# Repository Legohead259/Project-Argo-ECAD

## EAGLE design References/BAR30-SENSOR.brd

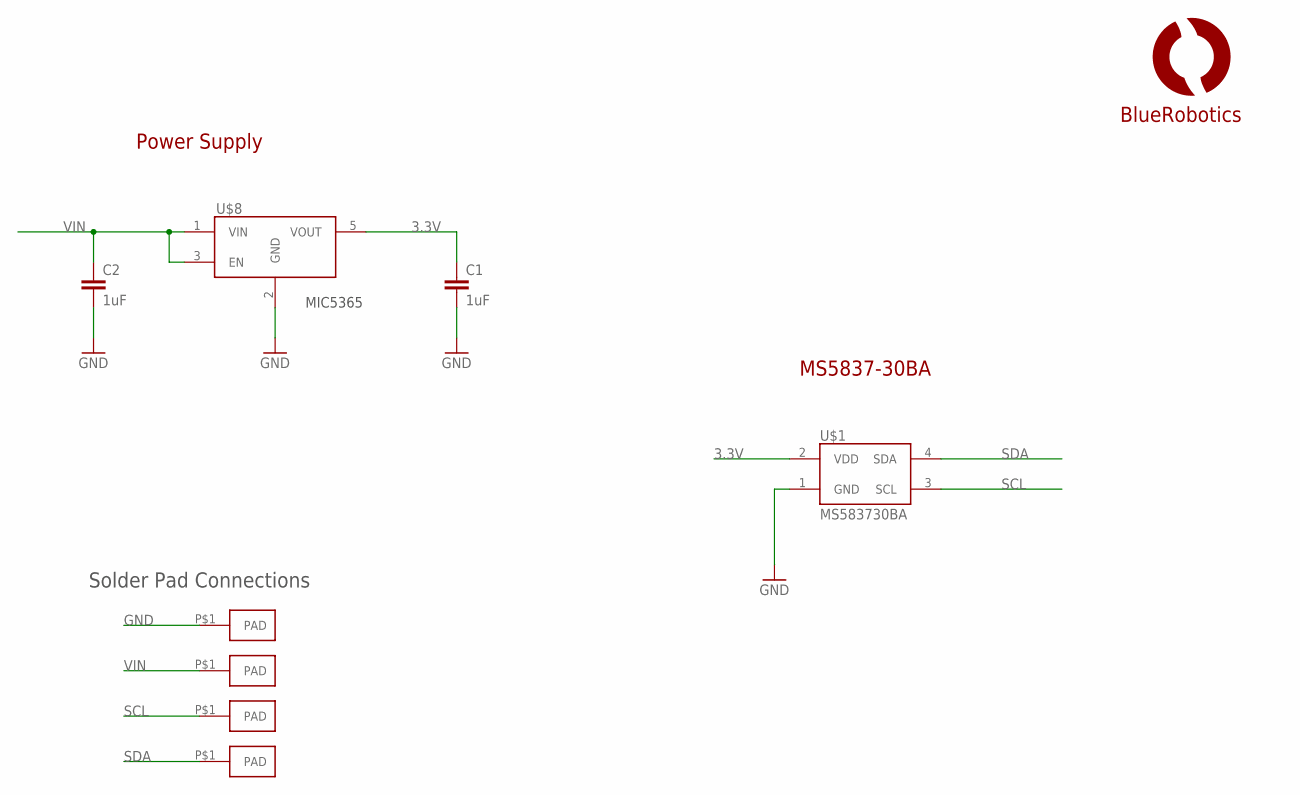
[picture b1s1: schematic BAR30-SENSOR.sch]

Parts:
C1, C2: 1uF; C0402
U$1: MS583730BA; MS5837
U$3, U$4, U$5, U$6: PAD1.5X3MM; PAD-1.5X3MM
U$7: LOGOBR-LOGO-S; BR-LOGO-SMALL
U$8: VREG-MIC5365; SC70-5L

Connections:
3.3V: C1.1, U$1.2 (VDD), U$8.5 (VOUT)
GND: C1.2, C2.2, U$1.1 (GND), U$3.P$1, U$8.2 (GND)
SCL: U$1.3 (SCL), U$5.P$1
SDA: U$1.4 (SDA), U$6.P$1
VIN: C2.1, U$4.P$1, U$8.1 (VIN), U$8.3 (EN)

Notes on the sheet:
Solder Pad Connections
MS5837-30BA
Power Supply
MIC5365

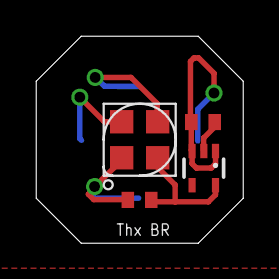
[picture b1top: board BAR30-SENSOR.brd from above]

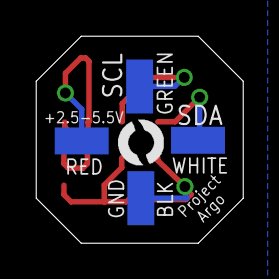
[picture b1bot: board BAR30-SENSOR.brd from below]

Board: 2 copper layers, 11.5 x 11.5 mm, 9 parts (5 on the bottom side), 5 nets.

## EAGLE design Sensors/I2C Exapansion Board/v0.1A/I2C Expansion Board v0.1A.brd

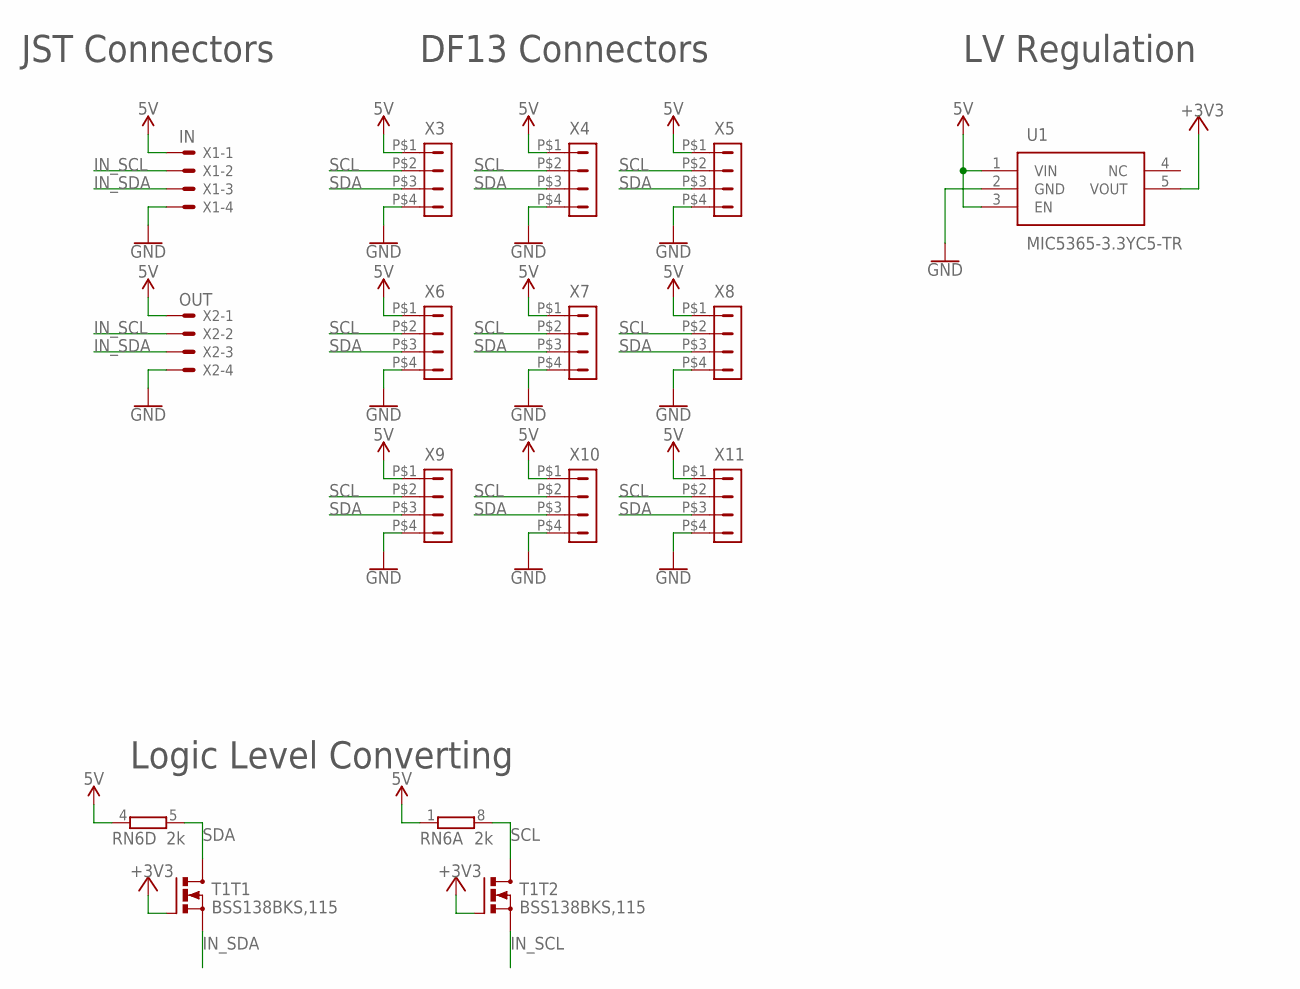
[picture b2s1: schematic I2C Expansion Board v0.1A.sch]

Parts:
RN6: 2k; EXB28V
T1: BSS138BKS,115; SOT363
U1: MIC5365-3.3YC5-TR; SOT65P210X110-5N
X1: IN; JST-XH-04-PACKAGE-LONG-PAD
X2: OUT; JST-XH-04-PACKAGE-LONG-PAD
X3, X4, X5, X6, X7, X8, X9, X10, X11: DF13-4P-1.25DSA

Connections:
5V: RN6.1, RN6.4 (1), U1.1 (VIN), U1.3 (EN), X1.1, X2.1, X3.P$1 (1), X4.P$1 (1), X5.P$1 (1), X6.P$1 (1), X7.P$1 (1), X8.P$1 (1), X9.P$1 (1), X10.P$1 (1), X11.P$1 (1)
+3V3: T1.2 (G), T1.5 (G), U1.5 (VOUT)
GND: U1.2 (GND), X1.4, X2.4, X3.P$4 (4), X4.P$4 (4), X5.P$4 (4), X6.P$4 (4), X7.P$4 (4), X8.P$4 (4), X9.P$4 (4), X10.P$4 (4), X11.P$4 (4)
IN_SCL: T1.4 (S), X1.2, X2.2
IN_SDA: T1.1 (S), X1.3, X2.3
SCL: RN6.8 (2), T1.3 (D), X3.P$2 (2), X4.P$2 (2), X5.P$2 (2), X6.P$2 (2), X7.P$2 (2), X8.P$2 (2), X9.P$2 (2), X10.P$2 (2), X11.P$2 (2)
SDA: RN6.5 (2), T1.6 (D), X3.P$3 (3), X4.P$3 (3), X5.P$3 (3), X6.P$3 (3), X7.P$3 (3), X8.P$3 (3), X9.P$3 (3), X10.P$3 (3), X11.P$3 (3)

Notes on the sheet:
Logic Level Converting
DF13 Connectors
JST Connectors
LV Regulation

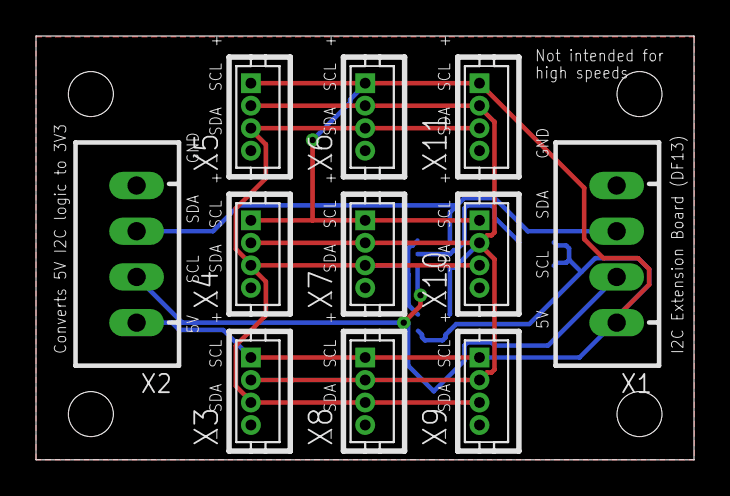
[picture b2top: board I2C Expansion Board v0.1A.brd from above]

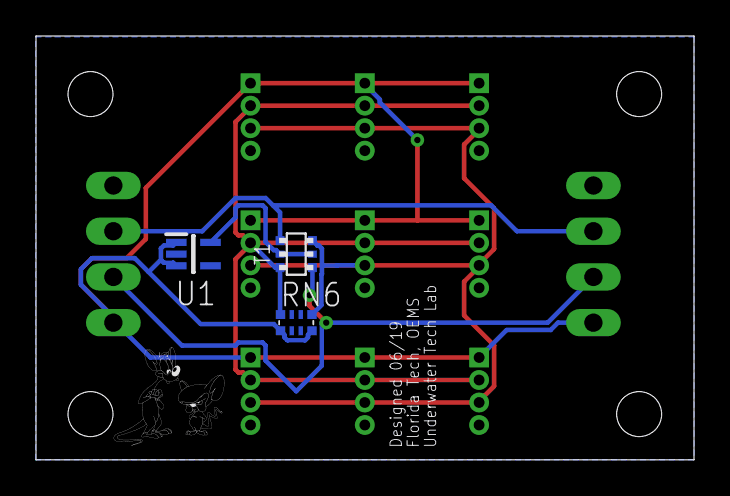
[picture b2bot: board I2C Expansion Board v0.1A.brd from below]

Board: 2 copper layers, 36.6 x 23.5 mm, 14 parts (3 on the bottom side), 7 nets.

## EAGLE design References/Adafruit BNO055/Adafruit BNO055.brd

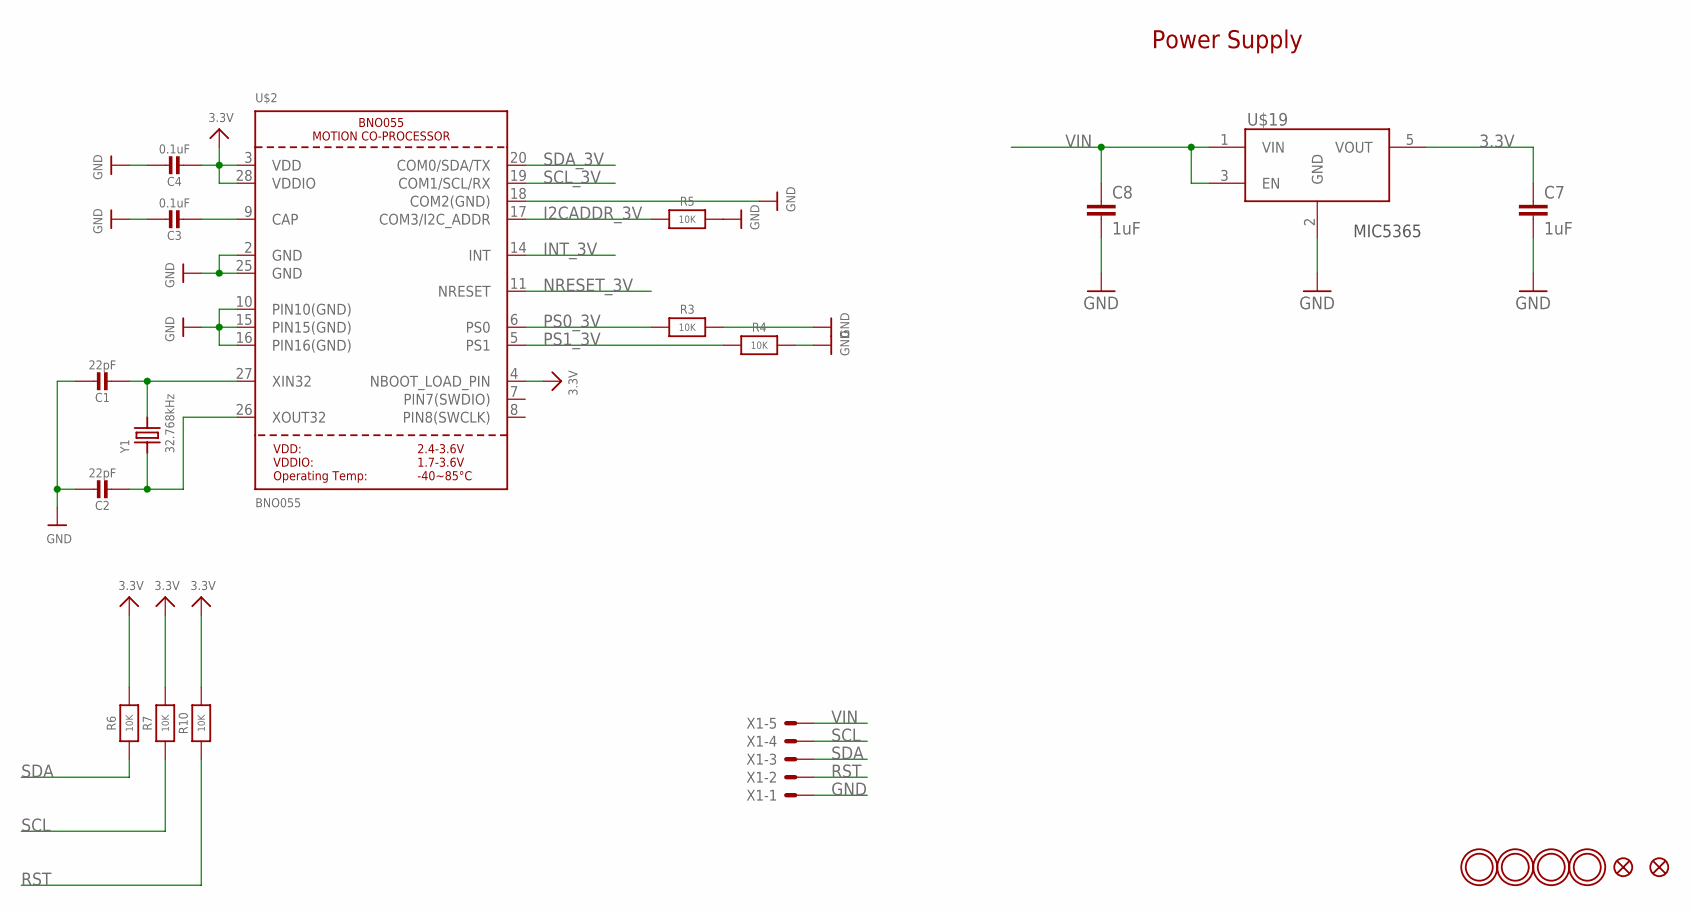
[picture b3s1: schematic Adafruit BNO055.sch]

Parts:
C1, C2: 22pF; 0805-NO
C3: 0.1uF; 0805-NO
C4: 0.1uF; 0805_10MGAP
C7, C8: 1uF; C0402
FID1, FID2: FIDUCIAL""; FIDUCIAL_1MM
R3, R4, R5, R6, R7, R10: 10K; 0805-NO
U$2: BNO055
U$19: VREG-MIC5365; SC70-5L
U$29, U$30, U$31, U$32: MOUNTINGHOLE2.5_THICK; MOUNTINGHOLE_2.5_PLATED_THICK
X1: JST-XH-05-PIN-LONG-PAD; JST-XH-05-PACKAGE-LONG-PAD
Y1: 32.768kHz; CRYSTAL_8X3.8

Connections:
3.3V: C4.2, C7.1, R6.2, R7.2, R10.2, U$2.3 (VDD), U$2.4 (NBOOT_LOAD_PIN), U$2.28 (VDDIO), U$19.5 (VOUT)
GND: C1.1, C2.1, C3.1, C4.1, C7.2, C8.2, R3.2, R4.2, R5.2, U$2.2 (GND), U$2.10 (PIN10(GND)), U$2.15 (PIN15(GND)), U$2.16 (PIN16(GND)), U$2.18 (COM2(GND)), U$2.25 (GND), U$19.2 (GND), X1.1
I2CADDR_3V: R5.1, U$2.17 (COM3/I2C_ADDR)
INT_3V: U$2.14 (INT)
unnamed: C1.2, U$2.27 (XIN32), Y1.P$4 (2)
unnamed: C2.2, U$2.26 (XOUT32), Y1.P$1 (1)
unnamed: C3.2, U$2.9 (CAP)
NRESET_3V: U$2.11 (NRESET)
PS0_3V: R3.1, U$2.6 (PS0)
PS1_3V: R4.1, U$2.5 (PS1)
RST: R10.1, X1.2
SCL: R7.1, X1.4
SCL_3V: U$2.19 (COM1/SCL/RX)
SDA: R6.1, X1.3
SDA_3V: U$2.20 (COM0/SDA/TX)
VIN: C8.1, U$19.1 (VIN), U$19.3 (EN), X1.5

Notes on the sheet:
Power Supply
MIC5365

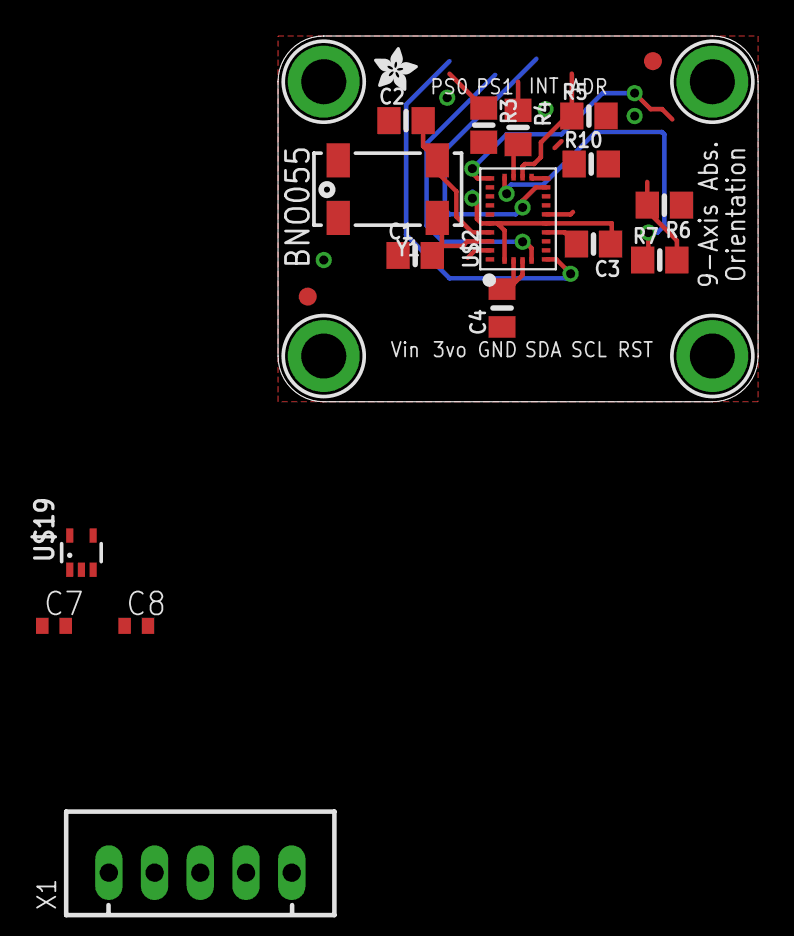
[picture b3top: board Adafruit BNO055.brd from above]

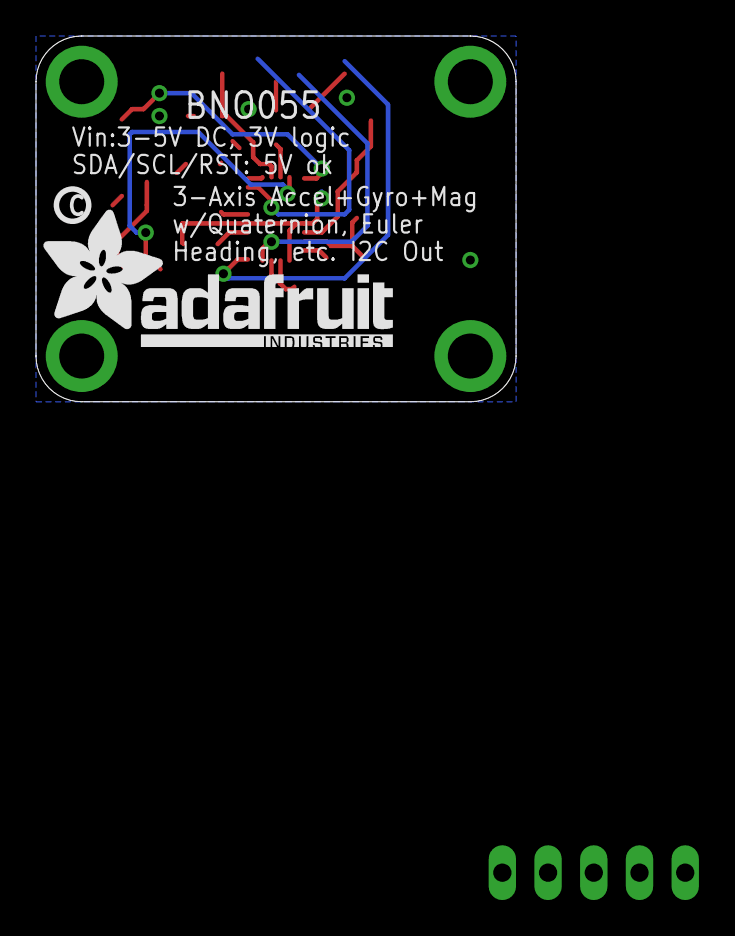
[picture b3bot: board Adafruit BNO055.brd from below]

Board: 2 copper layers, 26.7 x 20.3 mm, 25 parts (2 on the bottom side), 12 nets.

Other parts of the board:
U$3: PCBFEAT-REV-040
U$28: ADAFRUIT_TEXT_20MM
U$33: ADAFRUIT_2.5MM

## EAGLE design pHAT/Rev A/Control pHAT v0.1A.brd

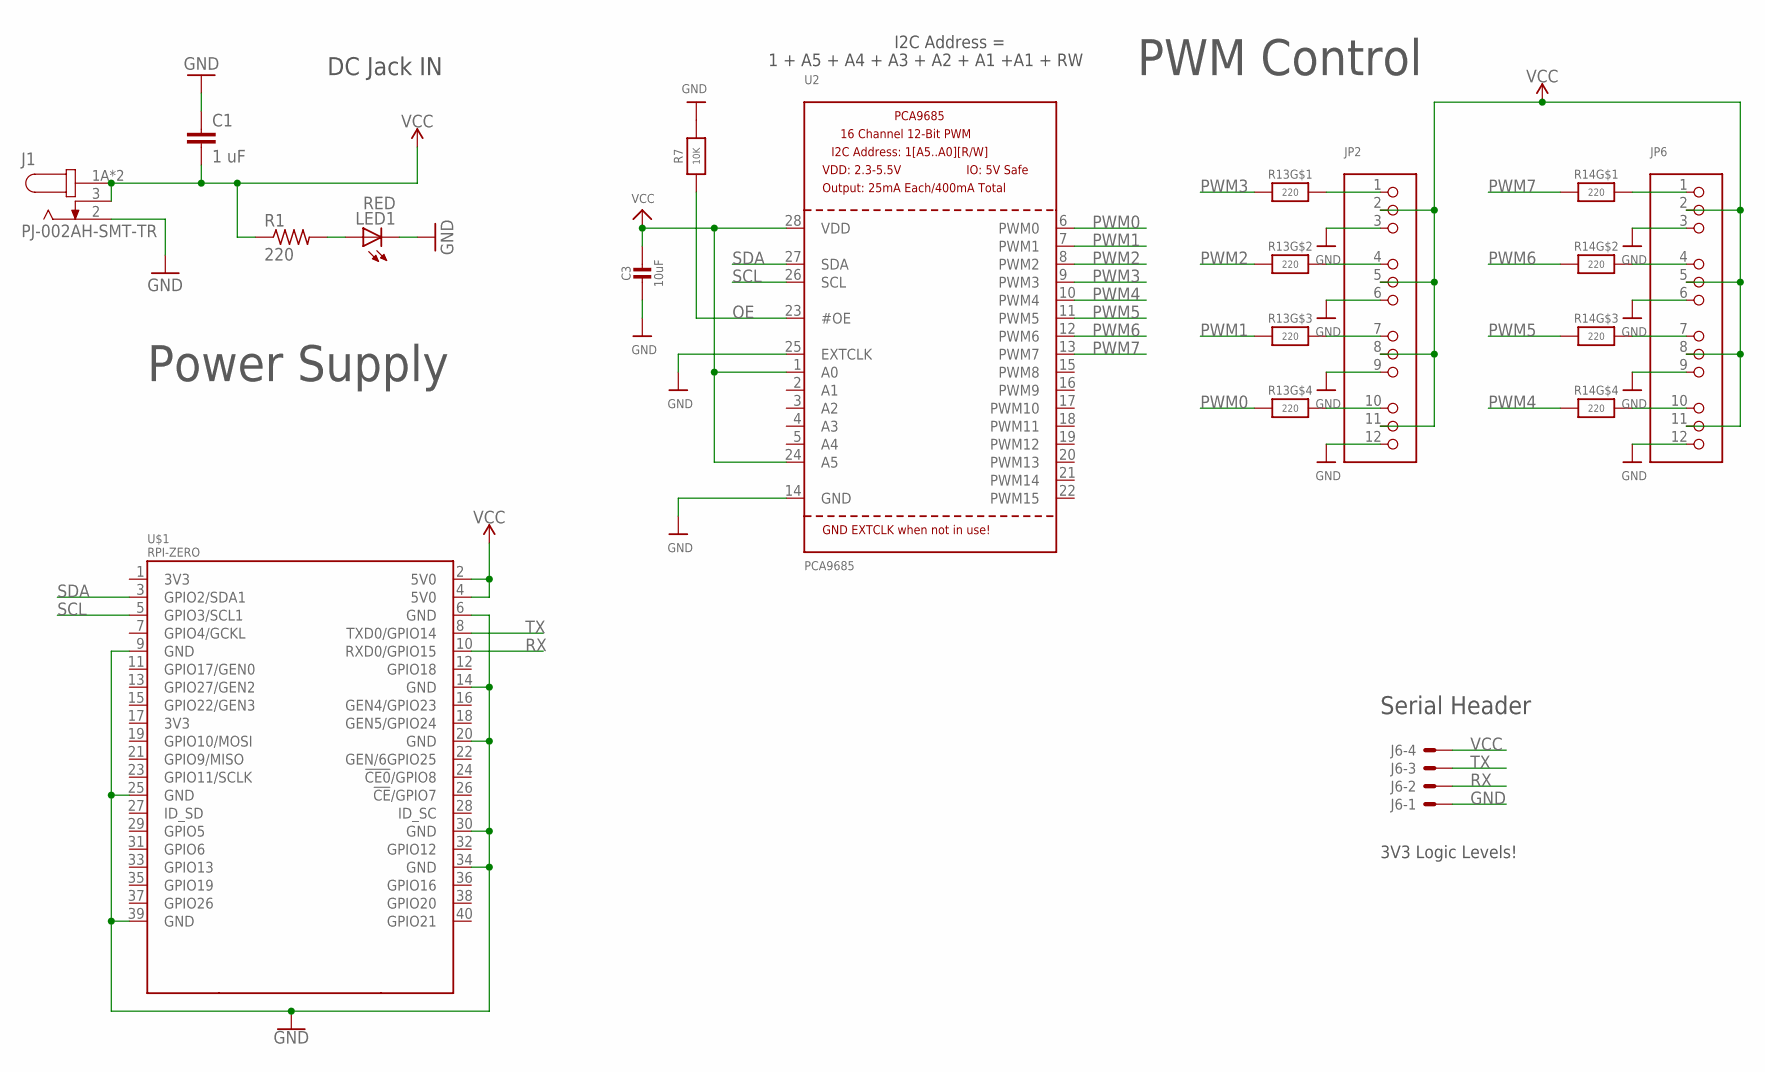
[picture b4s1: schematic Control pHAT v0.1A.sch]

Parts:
C1: 1 uF; C0603
C3: 10uF; 0805-NO
J1: PJ-002AH-SMT-TR; CUI_PJ-002AH-SMT-TR
J6: JST-XH-04-PIN-LONG-PAD; JST-XH-04-PACKAGE-LONG-PAD
JP2, JP6: HEADER-3X04; 3X04
LED1: RED; CHIP-LED0603
R1: 220; M1206
R7: 10K; 0805-NO
R13, R14: 220; RESPACK_4X0603
U2: PCA9685; TSSOP28
U$1: RPI-ZERO; RASPBERRYPI_BASTELSTUBE_V13_RASPI_BOARD_B+_FULL

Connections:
GND: C1.1, C3.2, J1.2, J6.1, JP2.3, JP2.6, JP2.9, JP2.12, JP6.3, JP6.6, JP6.9, JP6.12, LED1.C, R7.2, U2.14 (GND), U2.25 (EXTCLK)
GND@1: U$1.6 (GND), U$1.9 (GND), U$1.14 (GND), U$1.20 (GND), U$1.25 (GND), U$1.30 (GND), U$1.34 (GND), U$1.39 (GND)
unnamed: JP2.1, R13.8 (2)
unnamed: LED1.A, R1.2
unnamed: JP2.4, R13.7 (2)
unnamed: JP2.7, R13.6 (2)
unnamed: JP2.10, R13.5 (2)
unnamed: JP6.10, R14.5 (2)
unnamed: JP6.7, R14.6 (2)
unnamed: JP6.4, R14.7 (2)
unnamed: JP6.1, R14.8 (2)
OE: R7.1, U2.23 (#OE)
PWM0: R13.4 (1), U2.6 (PWM0)
PWM1: R13.3 (1), U2.7 (PWM1)
PWM2: R13.2 (1), U2.8 (PWM2)
PWM3: R13.1, U2.9 (PWM3)
PWM4: R14.4 (1), U2.10 (PWM4)
PWM5: R14.3 (1), U2.11 (PWM5)
PWM6: R14.2 (1), U2.12 (PWM6)
PWM7: R14.1, U2.13 (PWM7)
RX: J6.2, U$1.10 (RXD0/GPIO15)
SCL: U2.26 (SCL), U$1.5 (GPIO3/SCL1)
SDA: U2.27 (SDA), U$1.3 (GPIO2/SDA1)
TX: J6.3, U$1.8 (TXD0/GPIO14)
VCC: C1.2, C3.1, J1.1A (1), J1.1B (1), J1.3, J6.4, JP2.2, JP2.5, JP2.8, JP2.11, JP6.2, JP6.5, JP6.8, JP6.11, R1.1, U2.1 (A0), U2.24 (A5), U2.28 (VDD), U$1.2 (5V0), U$1.4 (5V0)

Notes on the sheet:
1 + A5 + A4 + A3 + A2 + A1 +A1 + RW
I2C Address =
DC Jack IN
Power Supply
PWM Control
Serial Header
3V3 Logic Levels!

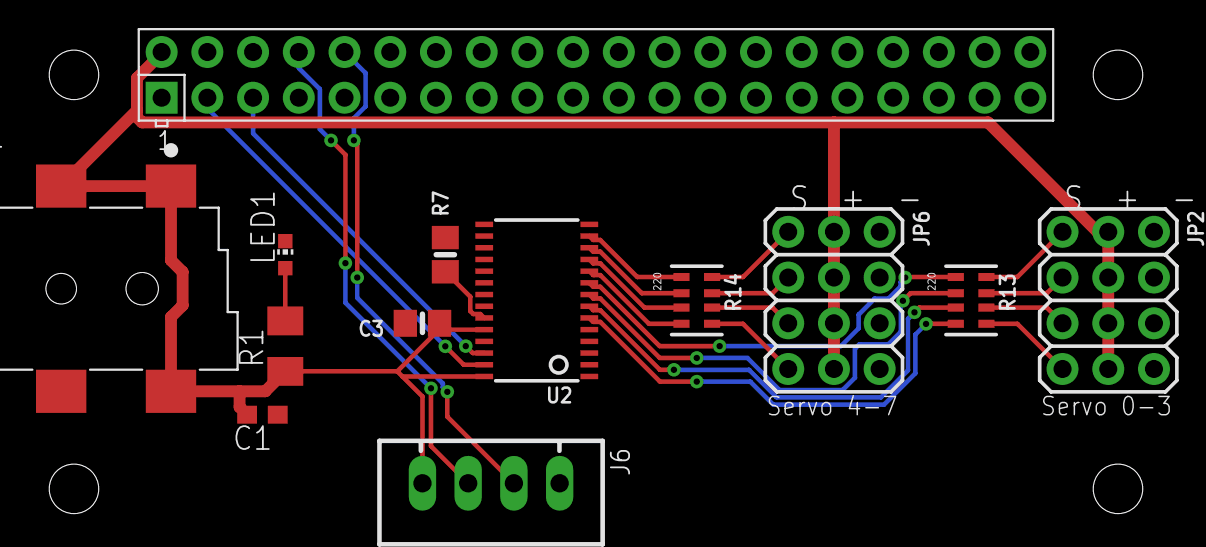
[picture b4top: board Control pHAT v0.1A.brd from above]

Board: 2 copper layers, 13 parts (0 on the bottom side), 25 nets.

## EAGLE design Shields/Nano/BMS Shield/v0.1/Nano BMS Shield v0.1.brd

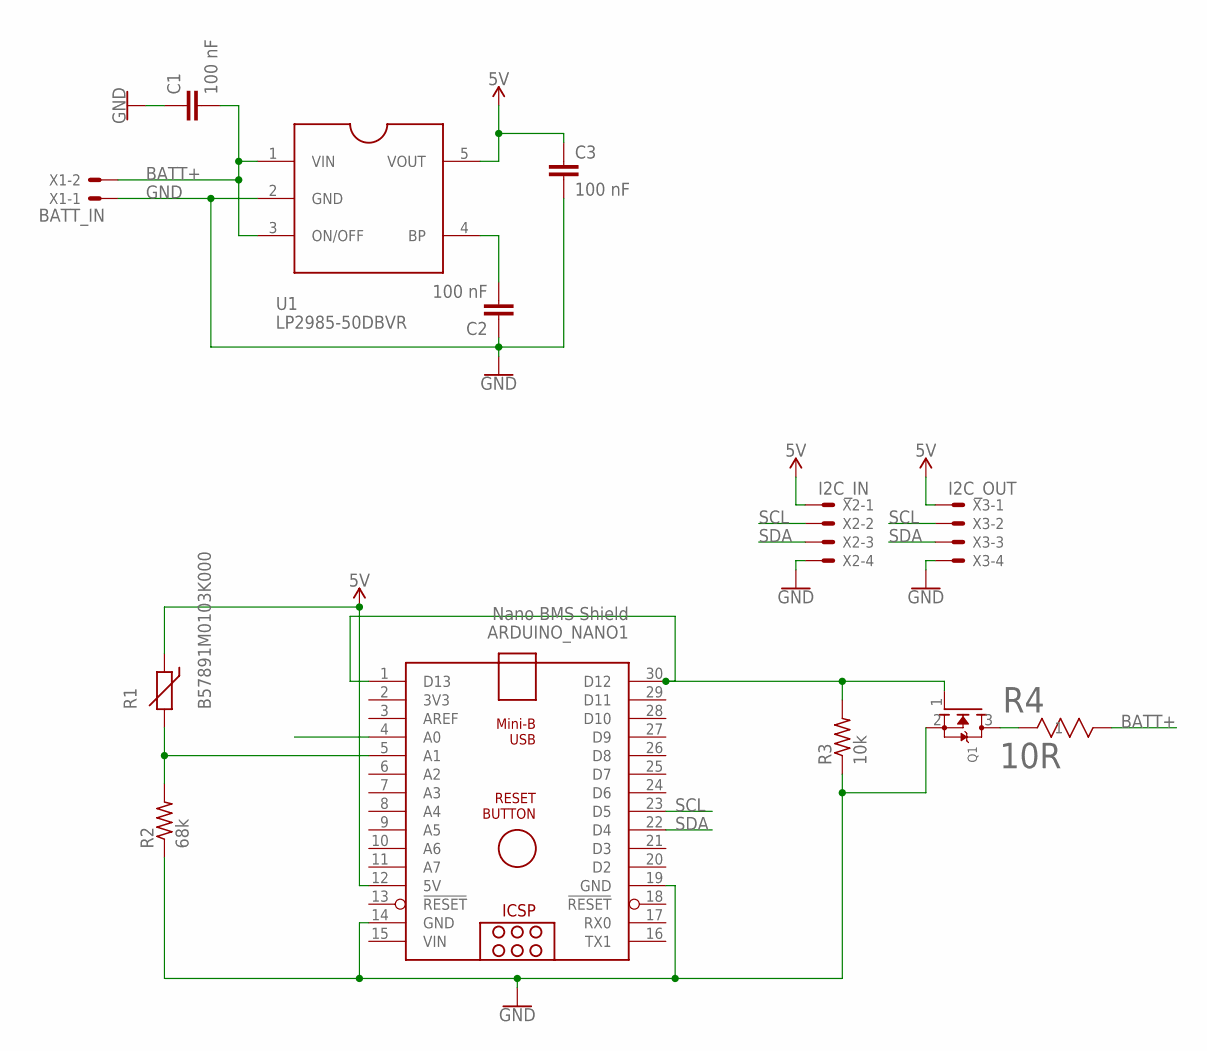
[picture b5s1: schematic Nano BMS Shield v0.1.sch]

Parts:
ARDUINO_NANO1: Nano BMS Shield; ARDUINO_NANO
C1, C2, C3: 100 nF; C0603
Q1: MOSFET-NREFLOW; SOT23
R1: B57891M0103K000; RS-2,5
R2: 68k; R0603
R3: 10k; R0603
R4: 10R; YAG_FMP300
U1: LP2985-50DBVR; SOT23-5
X1: BATT_IN; JST-XH-02-PACKAGE-LONG-PAD
X2: I2C_IN; JST-XH-04-PACKAGE-LONG-PAD
X3: I2C_OUT; JST-XH-04-PACKAGE-LONG-PAD

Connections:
5V: ARDUINO_NANO1.12 (5V), C3.1, R1.1, U1.5 (VOUT), X2.1, X3.1
BATT+: C1.2, R4.2, U1.1 (VIN), U1.3 (ON/OFF), X1.2
GND: ARDUINO_NANO1.14 (GND), ARDUINO_NANO1.19 (GND), C1.1, C2.1, C3.2, Q1.2 (S), R2.1, R3.1, U1.2 (GND), X1.1, X2.4, X3.4
unnamed: ARDUINO_NANO1.1 (D13), ARDUINO_NANO1.30 (D12), Q1.1 (G), R3.2
unnamed: Q1.3 (D), R4.1
unnamed: ARDUINO_NANO1.5 (A1), R1.2, R2.2
unnamed: C2.2, U1.4 (BP)
SCL: ARDUINO_NANO1.23 (D5), X2.2, X3.2
SDA: ARDUINO_NANO1.22 (D4), X2.3, X3.3
VIN: ARDUINO_NANO1.15 (VIN)

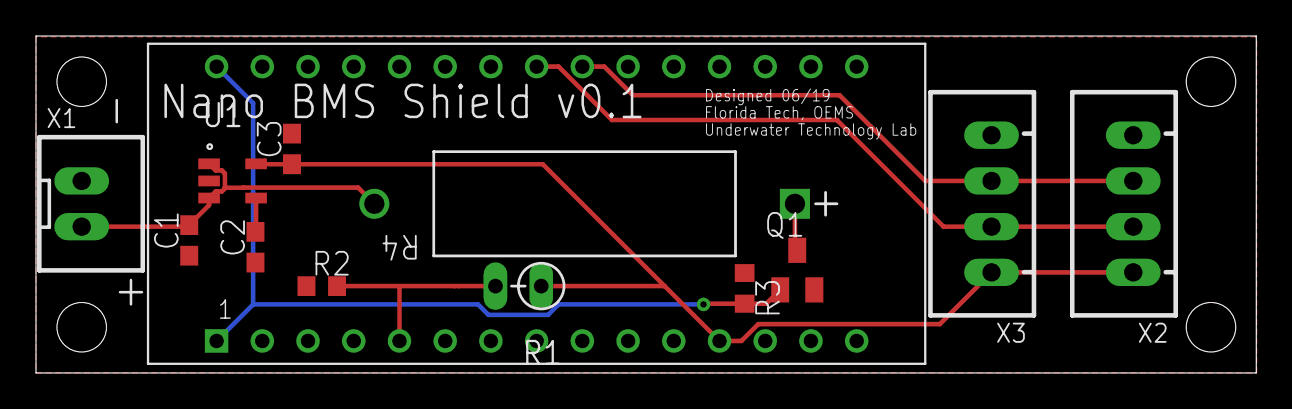
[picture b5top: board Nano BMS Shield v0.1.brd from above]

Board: 2 copper layers, 67.8 x 18.7 mm, 13 parts (0 on the bottom side), 9 nets.

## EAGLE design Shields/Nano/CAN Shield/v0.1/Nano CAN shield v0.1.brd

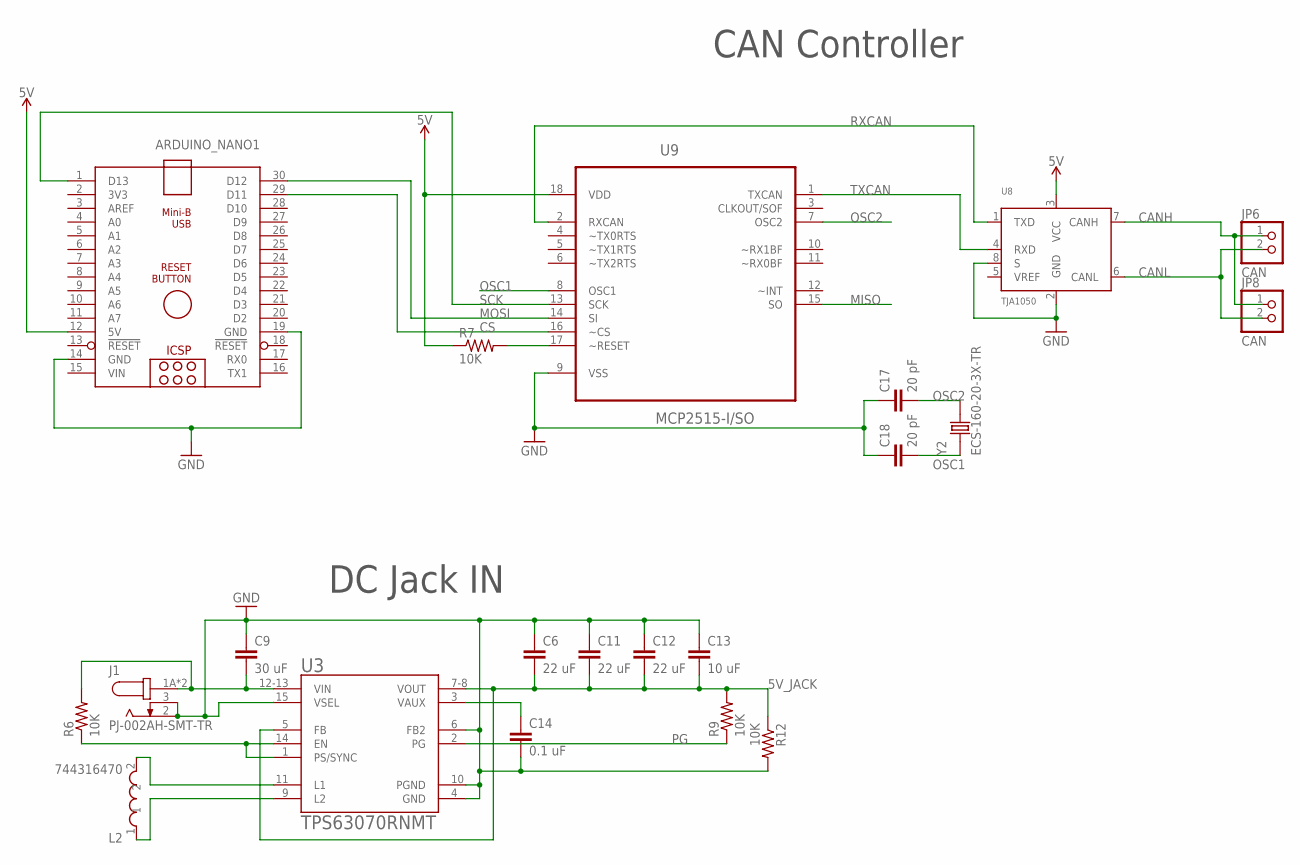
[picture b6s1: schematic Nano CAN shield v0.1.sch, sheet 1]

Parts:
ARDUINO_NANO1: ARDUINO_NANO
C6, C11, C12: 22 uF; C0603
C9: 30 uF; C0603
C13: 10 uF; C0603
C14: 0.1 uF; C0603
C17, C18: 20 pF; C0603
J1: PJ-002AH-SMT-TR; CUI_PJ-002AH-SMT-TR
JP6, JP8: CAN; 1X02
L2: 744316470; INDC2220X16
R6, R7, R9, R12: 10K; R0603
U3: TPS63070RNMT; QFN50P250X300X100-15N
U8: TJA1050; SOT96-1
U9: MCP2515-I/SO; SOIC127P1034X264-18N
Y2: ECS-160-20-3X-TR; XTAL_ECS-160-20-3X-TR

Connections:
5V: ARDUINO_NANO1.12 (5V), R7.1, U8.3 (VCC), U9.18 (VDD)
5V_JACK: C6.2, C11.2, C12.2, C13.2, R9.2, R12.1, U3.5 (FB), U3.7-8 (VOUT)
CANH: JP6.1, JP8.1, U8.7 (CANH)
CANL: JP6.2, JP8.2, U8.6 (CANL)
CS: ARDUINO_NANO1.29 (D11), U9.16 (~CS)
GND: ARDUINO_NANO1.14 (GND), ARDUINO_NANO1.19 (GND), C6.1, C9.1, C11.1, C12.1, C13.1, C14.2, C17.1, C18.1, J1.2, J1.3, R12.2, U3.4 (GND), U3.6 (FB2), U3.10 (PGND), U3.15 (VSEL), U8.2 (GND), U8.8 (S), U9.9 (VSS)
MISO: U9.15 (SO)
MOSI: ARDUINO_NANO1.30 (D12), U9.14 (SI)
unnamed: C9.2, J1.1A (1), J1.1B (1), R6.2, U3.12-13 (VIN)
unnamed: L2.2, U3.11 (L1)
unnamed: L2.1, U3.9 (L2)
unnamed: C14.1, U3.3 (VAUX)
unnamed: R6.1, U3.1 (PS/SYNC), U3.14 (EN)
unnamed: R7.2, U9.17 (~RESET)
OSC1: C18.2, U9.8 (OSC1), Y2.1
OSC2: C17.2, U9.7 (OSC2), Y2.2
PG: R9.1, U3.2 (PG)
RXCAN: U8.1 (TXD), U9.2 (RXCAN)
SCK: ARDUINO_NANO1.1 (D13), U9.13 (SCK)
TXCAN: U8.4 (RXD), U9.1 (TXCAN)
VIN: ARDUINO_NANO1.15 (VIN)

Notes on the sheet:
CAN Controller
DC Jack IN

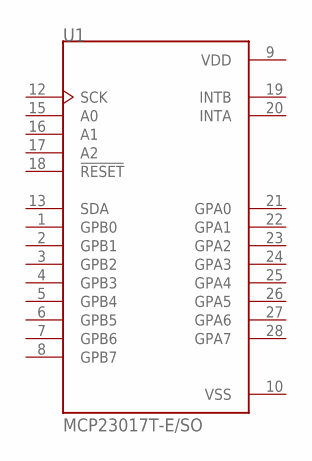
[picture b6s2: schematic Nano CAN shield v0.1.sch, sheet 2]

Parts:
U1: MCP23017T-E/SO; SOIC127P1030X265-28N

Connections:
VDD: U1.9 (VDD)
VSS: U1.10 (VSS)

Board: 2 copper layers, 22 parts (0 on the bottom side), 19 nets, no tracks yet.

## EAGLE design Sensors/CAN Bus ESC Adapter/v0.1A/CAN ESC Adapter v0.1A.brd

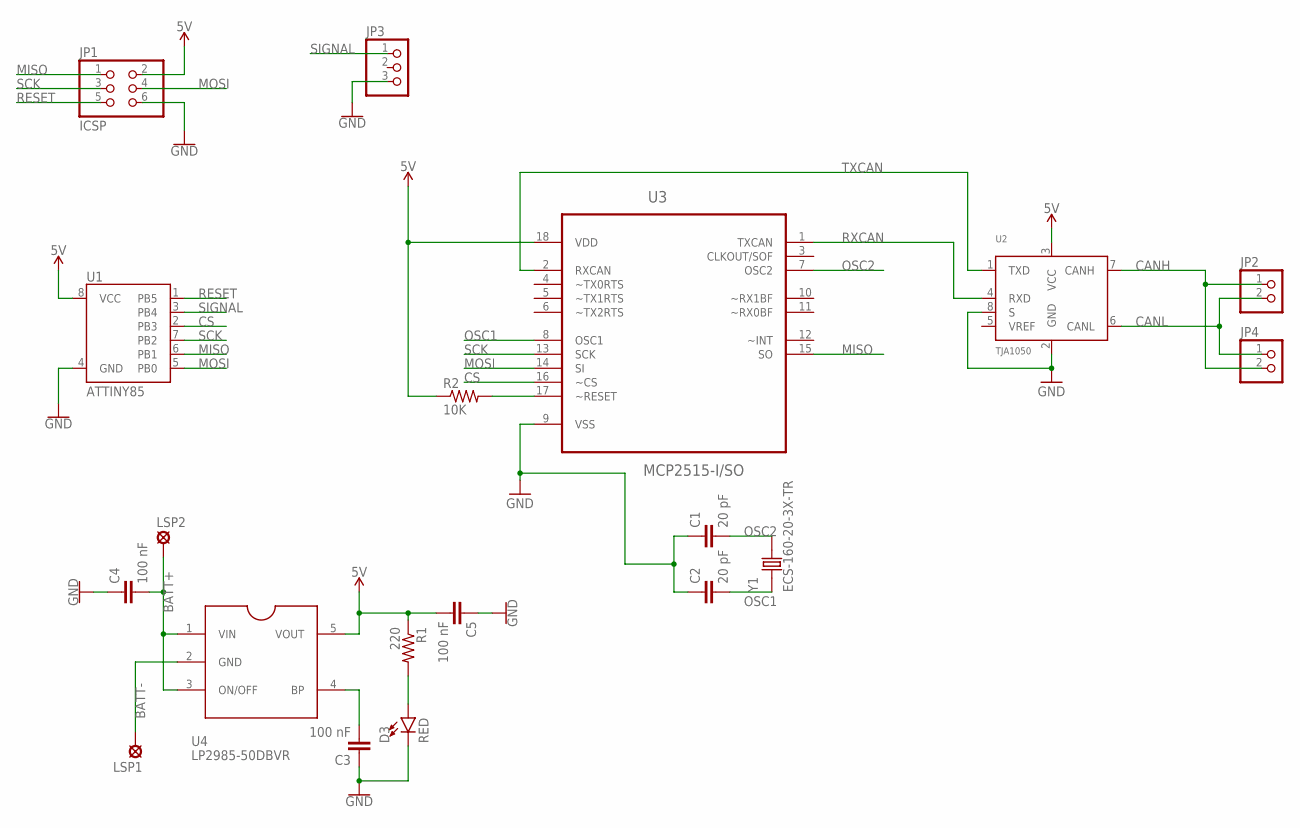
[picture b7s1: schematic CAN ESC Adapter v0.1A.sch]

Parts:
C1, C2: 20 pF; C0603
C3, C4, C5: 100 nF; C0603
D3: RED; LED-0603
JP1: ICSP; 2X03
JP2, JP4: PINHD-1X2/90; 1X02/90
JP3: PINHD-1X3/90; 1X03/90
LSP1, LSP2: SE14
R1: 220; R0603
R2: 10K; R0603
U1: ATTINY85
U2: TJA1050; SOT96-1
U3: MCP2515-I/SO; SOIC127P1034X264-18N
U4: LP2985-50DBVR; SOT23-5
Y1: ECS-160-20-3X-TR; XTAL_ECS-160-20-3X-TR

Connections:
5V: C5.2, JP1.2, R1.1, R2.1, U1.8 (VCC), U2.3 (VCC), U3.18 (VDD), U4.5 (VOUT)
BATT+: C4.2, LSP2.MP, U4.1 (VIN), U4.3 (ON/OFF)
BATT-: LSP1.MP, U4.2 (GND)
CANH: JP2.1, JP4.2, U2.7 (CANH)
CANL: JP2.2, JP4.1, U2.6 (CANL)
CS: U1.2 (PB3), U3.16 (~CS)
GND: C1.1, C2.1, C3.1, C4.1, C5.1, D3.C, JP1.6, JP3.3, U1.4 (GND), U2.2 (GND), U2.8 (S), U3.9 (VSS)
MISO: JP1.1, U1.6 (PB1), U3.15 (SO)
MOSI: JP1.4, U1.5 (PB0), U3.14 (SI)
unnamed: D3.A, R1.2
unnamed: R2.2, U3.17 (~RESET)
unnamed: C3.2, U4.4 (BP)
OSC1: C2.2, U3.8 (OSC1), Y1.1
OSC2: C1.2, U3.7 (OSC2), Y1.2
RESET: JP1.5, U1.1 (PB5)
RXCAN: U2.4 (RXD), U3.1 (TXCAN)
SCK: JP1.3, U1.7 (PB2), U3.13 (SCK)
SIGNAL: JP3.1, U1.3 (PB4)
TXCAN: U2.1 (TXD), U3.2 (RXCAN)

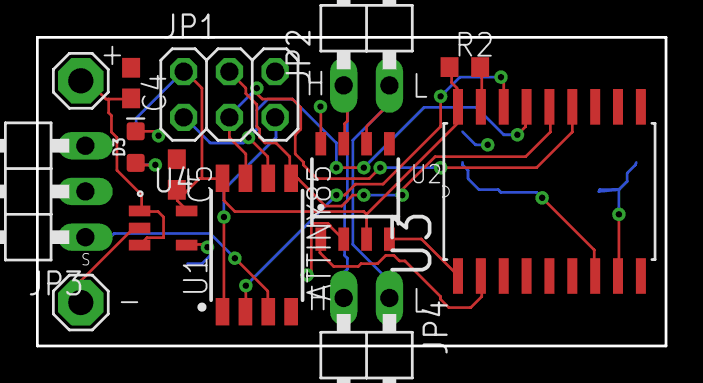
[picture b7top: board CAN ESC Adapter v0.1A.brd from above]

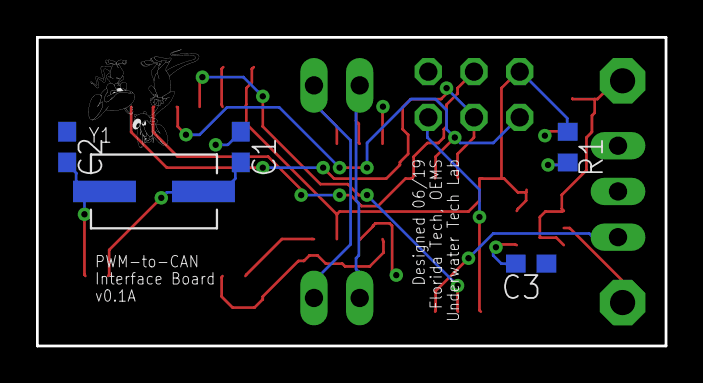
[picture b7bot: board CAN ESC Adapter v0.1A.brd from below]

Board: 2 copper layers, 34.9 x 17.1 mm, 19 parts (5 on the bottom side), 19 nets.

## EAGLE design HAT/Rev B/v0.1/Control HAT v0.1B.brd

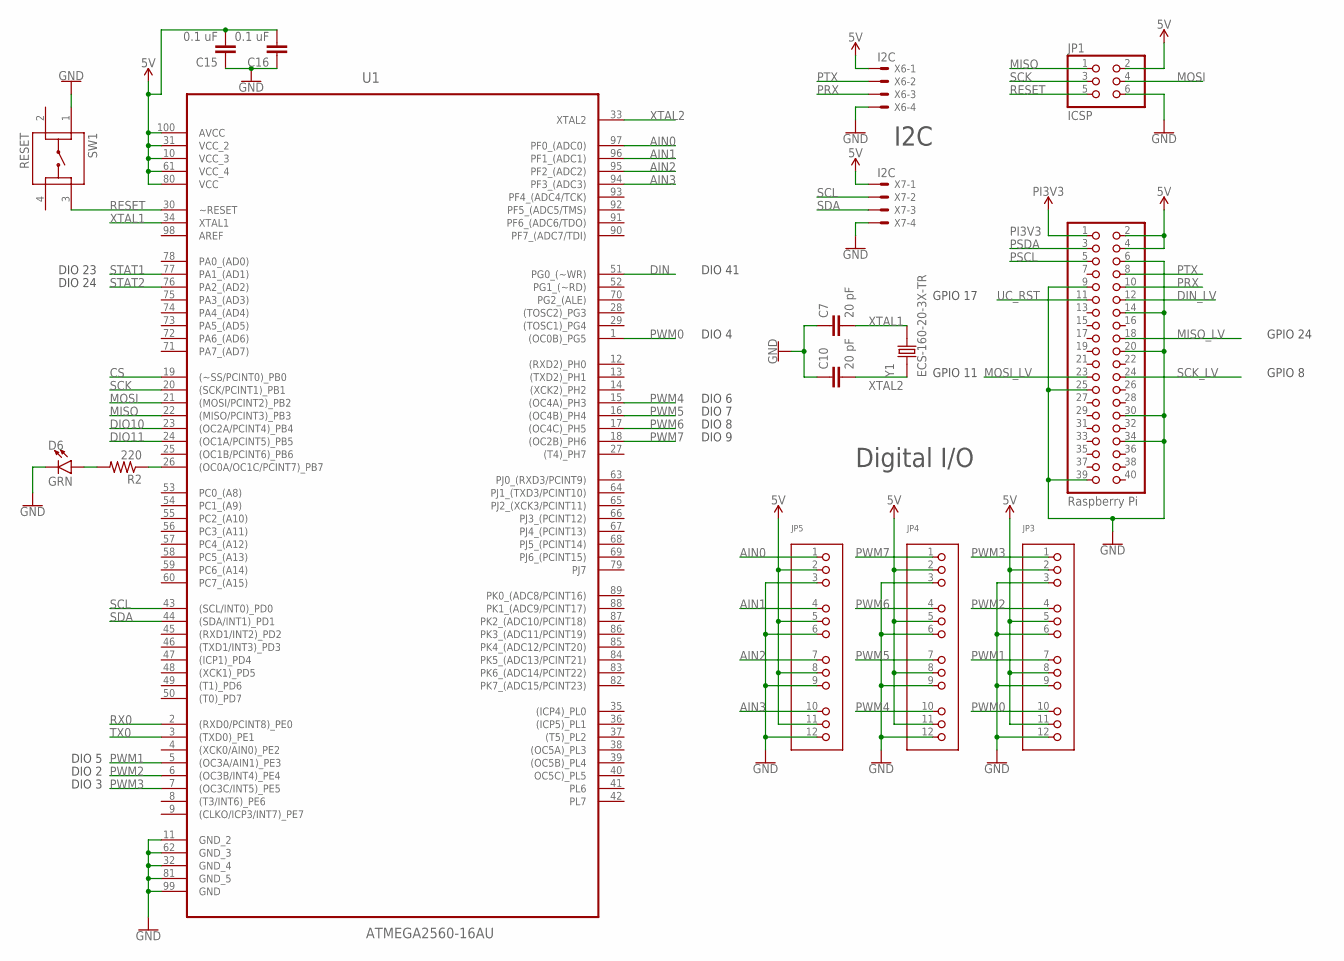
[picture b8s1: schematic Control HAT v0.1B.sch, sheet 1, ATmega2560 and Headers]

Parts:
C7, C10: 20 pF; C0603
C15, C16: 0.1 uF; C0603
D6: GRN; LED-0603
JP1: ICSP; 2X03
JP2: Raspberry Pi; 2X20
JP3, JP4, JP5: HEADER-3X04; 3X04
R2: 220; R0603
SW1: RESET; SW_1825910-6-4
U1: ATMEGA2560-16AU; QFP50P1600X1600X120-100N
X6, X7: I2C; JST-XH-04-PACKAGE-LONG-PAD
Y1: ECS-160-20-3X-TR; XTAL_ECS-160-20-3X-TR

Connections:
5V: C15.2, C16.2, JP1.2, JP2.2, JP2.4, JP3.2, JP3.5, JP3.8, JP3.11, JP4.2, JP4.5, JP4.8, JP4.11, JP5.2, JP5.5, JP5.8, JP5.11, U1.10 (VCC_3), U1.31 (VCC_2), U1.61 (VCC_4), U1.80 (VCC), U1.100 (AVCC), X6.1, X7.1; also elsewhere on the board
AIN0: JP5.1, U1.97 (PF0_(ADC0))
AIN1: JP5.4, U1.96 (PF1_(ADC1))
AIN2: JP5.7, U1.95 (PF2_(ADC2))
AIN3: JP5.10, U1.94 (PF3_(ADC3))
CS: U1.19 ((~SS/PCINT0)_PB0); also elsewhere on the board
DIN: U1.51 (PG0_(~WR)); also elsewhere on the board
DIN_LV: JP2.12; also elsewhere on the board
DIO10: U1.23 ((OC2A/PCINT4)_PB4)
DIO11: U1.24 ((OC1A/PCINT5)_PB5)
DIO13: R2.1, U1.26 ((OC0A/OC1C/PCINT7)_PB7)
GND: C7.1, C10.1, C15.1, C16.1, D6.C, JP1.6, JP2.6, JP2.9, JP2.14, JP2.20, JP2.25, JP2.30, JP2.34, JP2.39, JP3.3, JP3.6, JP3.9, JP3.12, JP4.3, JP4.6, JP4.9, JP4.12, JP5.3, JP5.6, JP5.9, JP5.12, SW1.1, U1.11 (GND_2), U1.32 (GND_4), U1.62 (GND_3), U1.81 (GND_5), U1.99 (GND), X6.4, X7.4; also elsewhere on the board
MISO: JP1.1, U1.22 ((MISO/PCINT3)_PB3); also elsewhere on the board
MISO_LV: JP2.18; also elsewhere on the board
MOSI: JP1.4, U1.21 ((MOSI/PCINT2)_PB2); also elsewhere on the board
MOSI_LV: JP2.23; also elsewhere on the board
unnamed: D6.A, R2.2
PI3V3: JP2.1; also elsewhere on the board
PRX: JP2.10, X6.3
PSCL: JP2.5; also elsewhere on the board
PSDA: JP2.3; also elsewhere on the board
PTX: JP2.8, X6.2
PWM0: JP3.10, U1.1 ((OC0B)_PG5)
PWM1: JP3.7, U1.5 ((OC3A/AIN1)_PE3)
PWM2: JP3.4, U1.6 ((OC3B/INT4)_PE4)
PWM3: JP3.1, U1.7 ((OC3C/INT5)_PE5)
PWM4: JP4.10, U1.15 ((OC4A)_PH3)
PWM5: JP4.7, U1.16 ((OC4B)_PH4)
PWM6: JP4.4, U1.17 ((OC4C)_PH5)
PWM7: JP4.1, U1.18 ((OC2B)_PH6)
RESET: JP1.5, SW1.3, U1.30 (~RESET); also elsewhere on the board
RX0: U1.2 ((RXD0/PCINT8)_PE0); also elsewhere on the board
SCK: JP1.3, U1.20 ((SCK/PCINT1)_PB1); also elsewhere on the board
SCK_LV: JP2.24; also elsewhere on the board
SCL: U1.43 ((SCL/INT0)_PD0), X7.2; also elsewhere on the board
SDA: U1.44 ((SDA/INT1)_PD1), X7.3; also elsewhere on the board
STAT1: U1.77 (PA1_(AD1)); also elsewhere on the board
STAT2: U1.76 (PA2_(AD2)); also elsewhere on the board
TX0: U1.3 ((TXD0)_PE1); also elsewhere on the board
UC_RST: JP2.11; also elsewhere on the board
XTAL1: C7.2, U1.34 (XTAL1), Y1.2
XTAL2: C10.2, U1.33 (XTAL2), Y1.1

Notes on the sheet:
DIO 5
DIO 2
DIO 3
DIO 4
DIO 6
DIO 7
DIO 8
DIO 9
Digital I/O
I2C
DIO 24
DIO 23
DIO 41
GPIO 8
GPIO 24
GPIO 11
GPIO 17

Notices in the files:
parts and their libraries:
SparkFun-LED: Licensing: Creative Commons ShareAlike 4.0 International - https://creativecommons.org/licenses/by-sa/4.0
microbuilder: This work is placed in the public domain, and may be freely used for commercial and non-commercial work with the following conditions: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
